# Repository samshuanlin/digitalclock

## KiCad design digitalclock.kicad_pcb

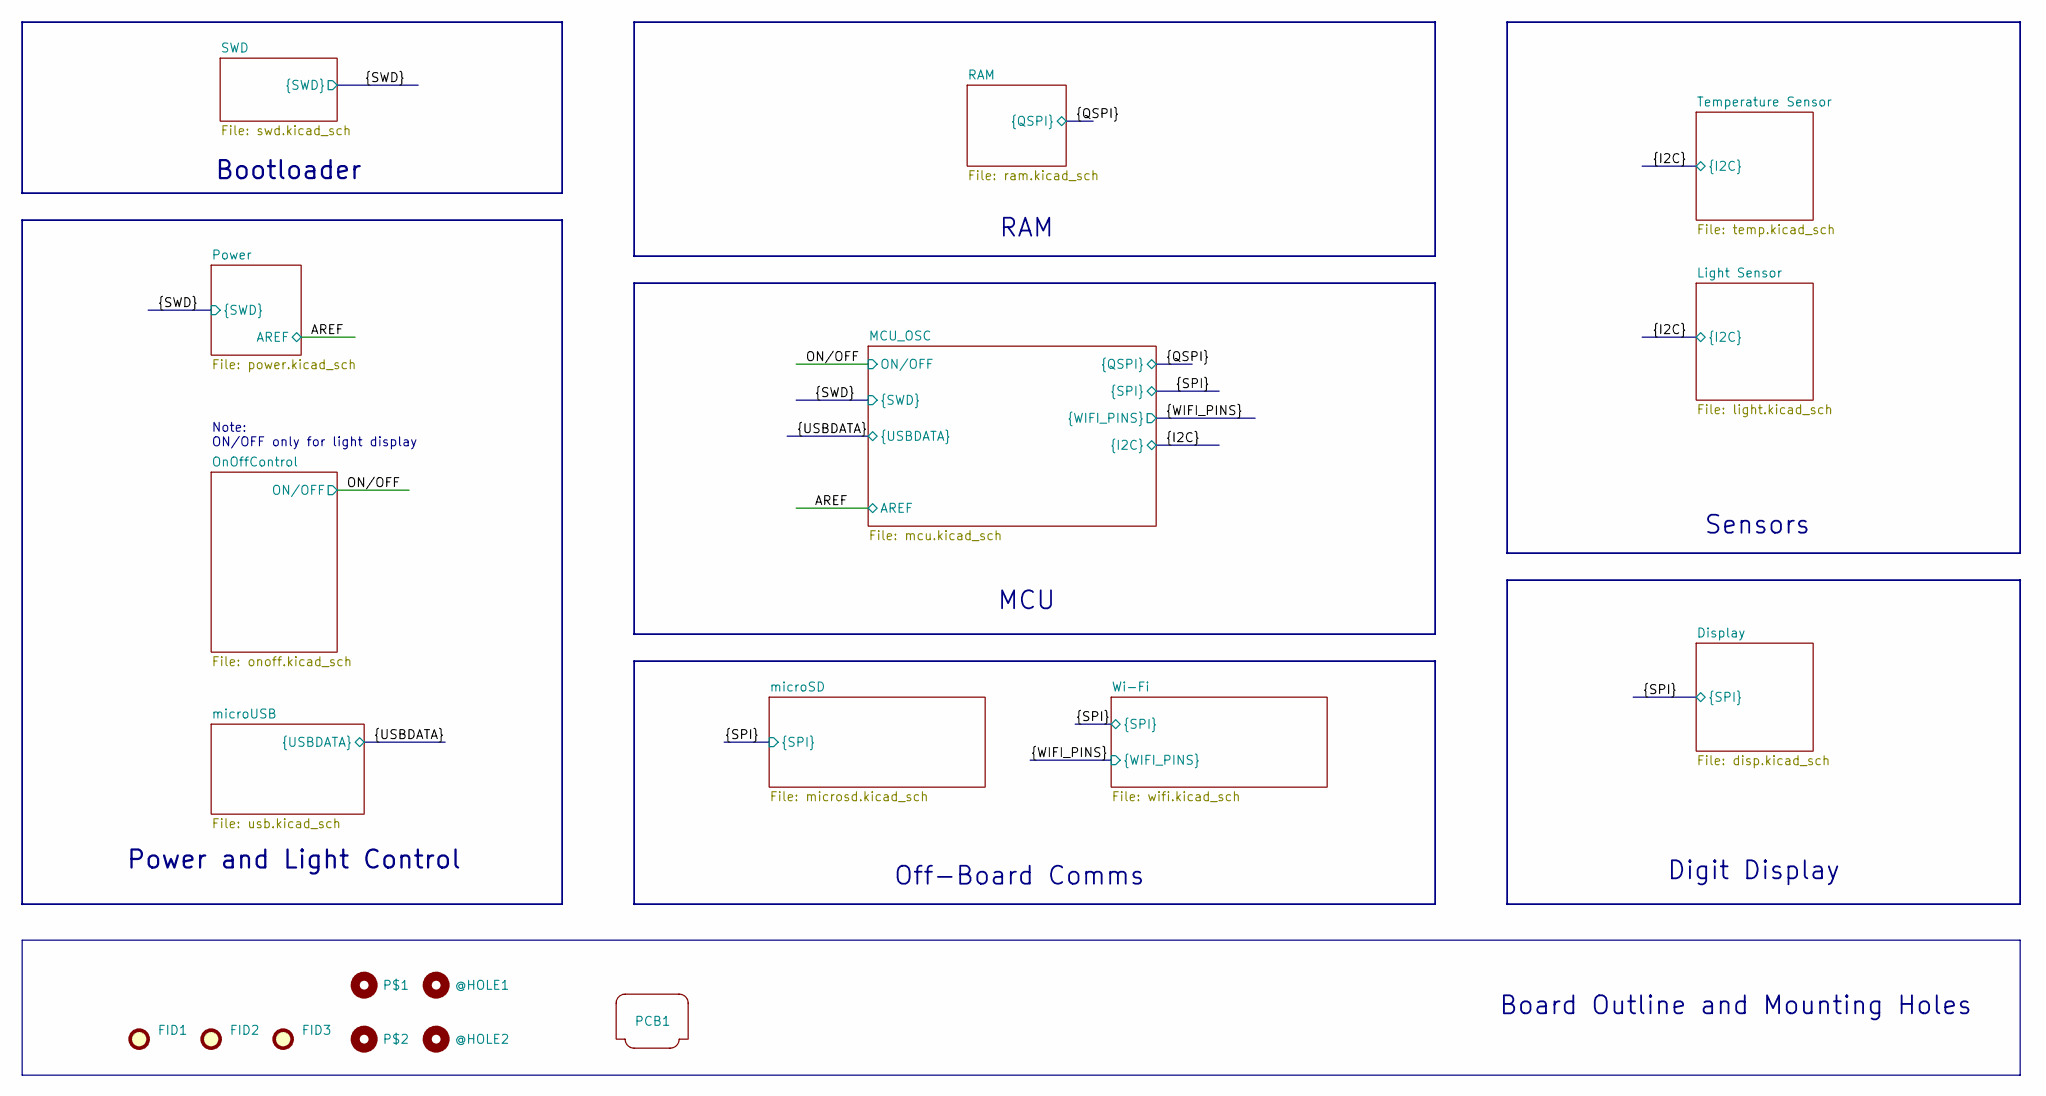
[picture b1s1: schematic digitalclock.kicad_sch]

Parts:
@HOLE1, @HOLE2: MountingHole; MountingHole_2.5mm
FID1, FID2, FID3: Fiducial; Fiducial_1mm_Mask2mm
P$1, P$2: MountingHole; MOUNTINGHOLE_2.5_PLATED
PCB1: Board_Outline

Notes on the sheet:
Sensors
Bootloader
Note: ON/OFF only for light display
RAM
MCU
Board Outline and Mounting Holes
Digit Display
Power and Light Control
Off-Board Comms

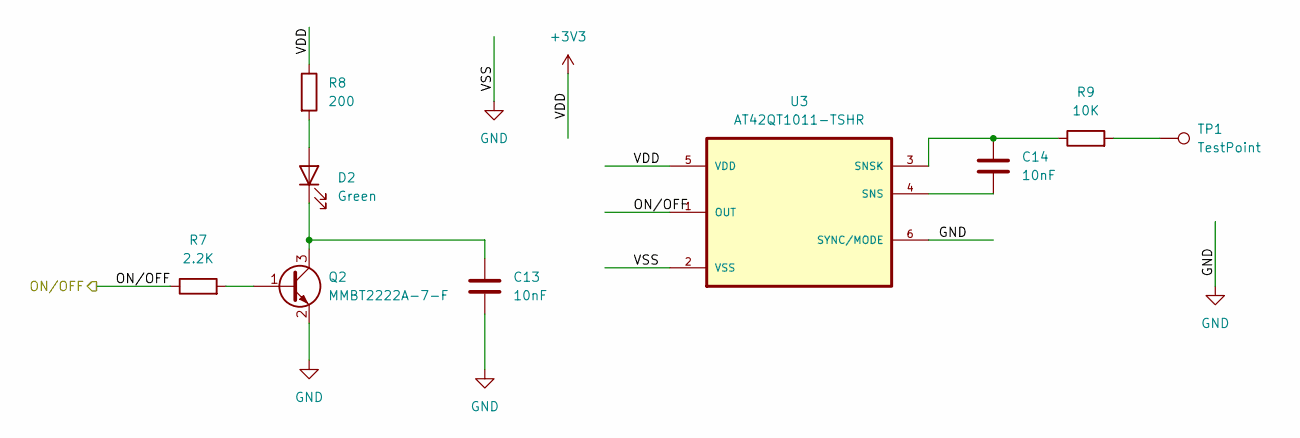
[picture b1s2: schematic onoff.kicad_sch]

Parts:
C13, C14: 10nF; 0603-NO; Mfr P/N C0402C103K3REC7411
D2: Green; 0603-NO; Mfr P/N 150060VS75000
Q2: MMBT2222A-7-F; SOT-23; Mfr P/N MMBT2222A-7-F
R7: 2.2K; 0603-NO; Mfr P/N CRGH0603F2K2
R8: 200; 0603-NO; Mfr P/N CR0603-FX-2000ELF
R9: 10K; 0603-NO; Mfr P/N RNCP0603FTD10K0
TP1: TestPoint; TestPoint_THTPad_1.0x1.0mm_Drill0.5mm
U3: AT42QT1011-TSHR; SOT95P280X145-6N; PARTREV B

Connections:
+3V3: R8.1, U3.5 (VDD); also elsewhere on the board
/ON/OFF: R7.1, U3.1 (OUT); also elsewhere on the board
GND: C13.2, Q2.2 (E), U3.2 (VSS), U3.6 (SYNC/MODE); also elsewhere on the board
unnamed: D2.2 (A), R8.2
unnamed: C13.1, D2.1 (K), Q2.3 (C)
unnamed: Q2.1 (B), R7.2
unnamed: R9.2, TP1.1
unnamed: C14.2, U3.4 (SNS)
unnamed: C14.1, R9.1, U3.3 (SNSK)

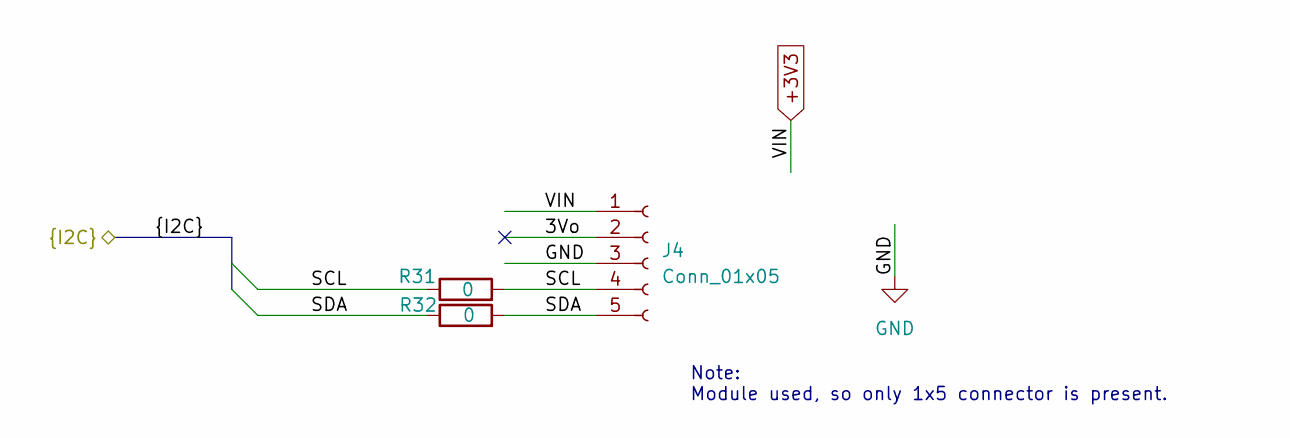
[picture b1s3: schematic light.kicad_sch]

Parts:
J4: Conn_01x05; CONN5_1LFBN-RC_SUL; Mfr P/N PPTC051LFBN-RC
R31, R32: 0; 0603-NO; Mfr P/N RC0603JR-070RL

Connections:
+3V3: J4.1; also elsewhere on the board
/Light Sensor/3Vo: J4.2
/SCL: J4.4, R31.1, R31.2; also elsewhere on the board
/SDA: J4.5, R32.1, R32.2; also elsewhere on the board
GND: J4.3; also elsewhere on the board

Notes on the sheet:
Note: Module used, so only 1x5 connector is present.

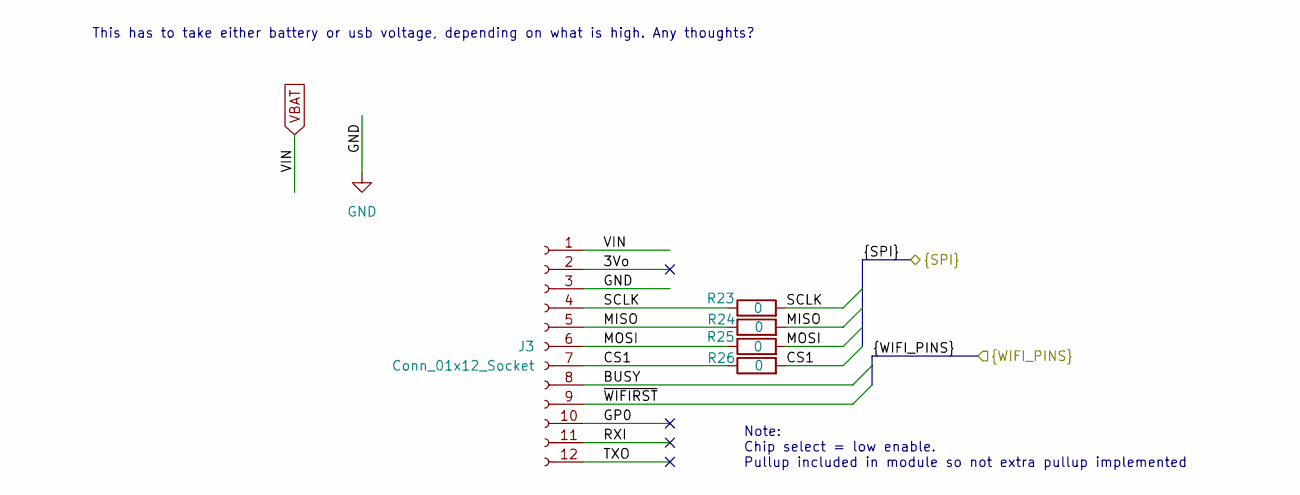
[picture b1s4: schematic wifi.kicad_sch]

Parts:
J3: Conn_01x12_Socket; PinSocket_1x12_P2.54mm_Vertical; Mfr P/N PPTC121LFBN-RC
R23, R24, R25, R26: 0; 0603-NO; Mfr P/N RC0603JR-070RL

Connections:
/BUSY: J3.8; also elsewhere on the board
/CS1: J3.7, R26.1, R26.2; also elsewhere on the board
/MISO: J3.5, R24.1, R24.2; also elsewhere on the board
/MOSI: J3.6, R25.1, R25.2; also elsewhere on the board
/SCLK: J3.4, R23.1, R23.2; also elsewhere on the board
/Wi-Fi/3Vo: J3.2
/Wi-Fi/GP0: J3.10
/Wi-Fi/RXI: J3.11
/Wi-Fi/TXO: J3.12
/~WIFIRST: J3.9; also elsewhere on the board
GND: J3.3; also elsewhere on the board
VBAT: J3.1; also elsewhere on the board

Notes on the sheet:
Note: Chip select = low enable. Pullup included in module so not extra pullup implemented
This has to take either battery or usb voltage, depending on what is high. Any thoughts?

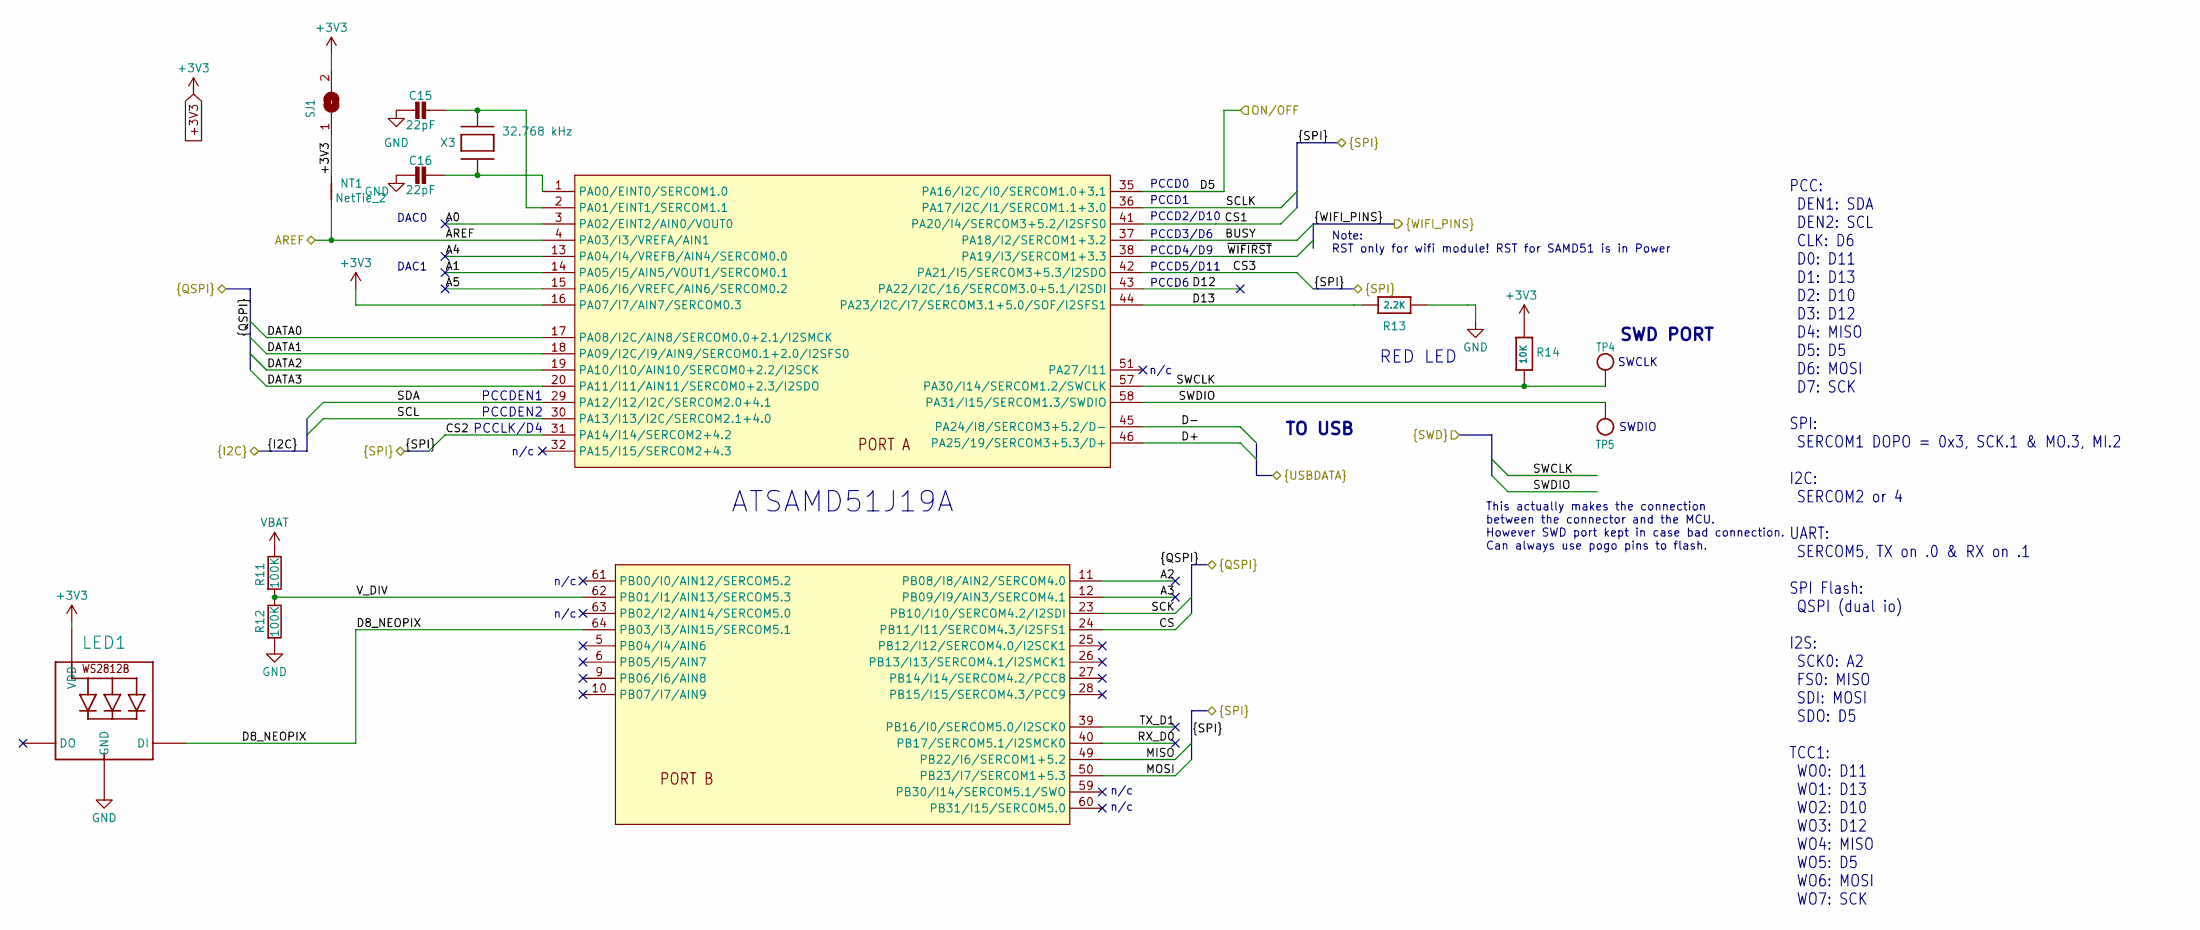
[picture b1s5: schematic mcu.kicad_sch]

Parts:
C15, C16: 22pF; 0603-NO; Mfr P/N C0603C220K4GAC7867
LED1: WS2812B3535; LED3535; Mfr P/N SK6812MINI
NT1: NetTie_2; NetTie-2_SMD_Pad0.5mm
R11, R12: 100K; 0603-NO; Mfr P/N CR0603-FX-1003ELF
R13: 2.2K; 0603-NO; Mfr P/N CRGH0603F2K2
R14: 10K; 0603-NO; Mfr P/N RNCP0603FTD10K0
SJ1: SOLDERJUMPERCLOSED; SOLDERJUMPER_CLOSEDWIRE
TP4, TP5: TESTPOINTROUND1.5MM; TESTPOINT_ROUND_1.5MM
U$1: ATSAMD51J19A-AUT; TQFP-64_10x10mm_P0.5mm; Mfr P/N ATSAMD51J19A-AUT
X3: 32.768 kHz; XTAL3215; Mfr P/N STDMUA17-32.768K

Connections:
+3V3: LED1.2 (VDD), NT1.2, R14.1, SJ1.1, SJ1.2, U$1.16 (PA07/I7/AIN7/SERCOM0.3); also elsewhere on the board
/AREF: NT1.1, U$1.4 (PA03/I3/VREFA/AIN1); also elsewhere on the board
/BUSY: U$1.37 (PA18/I2/SERCOM1+3.2); also elsewhere on the board
/CS: U$1.24 (PB11/I11/SERCOM4.3/I2SFS1); also elsewhere on the board
/CS1: U$1.41 (PA20/I4/SERCOM3+5.2/I2SFS0); also elsewhere on the board
/CS2: U$1.31 (PA14/I14/SERCOM2+4.2); also elsewhere on the board
/CS3: U$1.42 (PA21/I5/SERCOM3+5.3/I2SDO); also elsewhere on the board
/D+: U$1.46 (PA25/19/SERCOM3+5.3/D+); also elsewhere on the board
/D-: U$1.45 (PA24/I8/SERCOM3+5.2/D-); also elsewhere on the board
/DATA0: U$1.17 (PA08/I2C/AIN8/SERCOM0.0+2.1/I2SMCK); also elsewhere on the board
/DATA1: U$1.18 (PA09/I2C/I9/AIN9/SERCOM0.1+2.0/I2SFS0); also elsewhere on the board
/DATA2: U$1.19 (PA10/I10/AIN10/SERCOM0+2.2/I2SCK); also elsewhere on the board
/DATA3: U$1.20 (PA11/I11/AIN11/SERCOM0+2.3/I2SDO); also elsewhere on the board
/MCU_OSC/A0: U$1.3 (PA02/EINT2/AIN0/VOUT0)
/MCU_OSC/A1: U$1.14 (PA05/I5/AIN5/VOUT1/SERCOM0.1)
/MCU_OSC/A2: U$1.11 (PB08/I8/AIN2/SERCOM4.0)
/MCU_OSC/A3: U$1.12 (PB09/I9/AIN3/SERCOM4.1)
/MCU_OSC/A4: U$1.13 (PA04/I4/VREFB/AIN4/SERCOM0.0)
/MCU_OSC/A5: U$1.15 (PA06/I6/VREFC/AIN6/SERCOM0.2)
/MCU_OSC/D8_NEOPIX: LED1.1 (DI), U$1.64 (PB03/I3/AIN15/SERCOM5.1)
/MCU_OSC/D12: U$1.43 (PA22/I2C/16/SERCOM3.0+5.1/I2SDI)
/MCU_OSC/D13: R13.1, U$1.44 (PA23/I2C/I7/SERCOM3.1+5.0/SOF/I2SFS1)
/MCU_OSC/RX_D0: U$1.40 (PB17/SERCOM5.1/I2SMCK0)
/MCU_OSC/TX_D1: U$1.39 (PB16/I0/SERCOM5.0/I2SCK0)
/MCU_OSC/V_DIV: R11.2, R12.1, U$1.62 (PB01/I1/AIN13/SERCOM5.3)
/MISO: U$1.49 (PB22/I6/SERCOM1+5.2); also elsewhere on the board
/MOSI: U$1.50 (PB23/I7/SERCOM1+5.3); also elsewhere on the board
/ON/OFF: U$1.35 (PA16/I2C/I0/SERCOM1.0+3.1); also elsewhere on the board
/SCK: U$1.23 (PB10/I10/SERCOM4.2/I2SDI); also elsewhere on the board
/SCL: U$1.30 (PA13/I13/I2C/SERCOM2.1+4.0); also elsewhere on the board
/SCLK: U$1.36 (PA17/I2C/I1/SERCOM1.1+3.0); also elsewhere on the board
/SDA: U$1.29 (PA12/I12/I2C/SERCOM2.0+4.1); also elsewhere on the board
/SWCLK: R14.2, TP4.P$1, U$1.57 (PA30/I14/SERCOM1.2/SWCLK); also elsewhere on the board
/SWDIO: TP5.P$1, U$1.58 (PA31/I15/SERCOM1.3/SWDIO); also elsewhere on the board
/~WIFIRST: U$1.38 (PA19/I3/SERCOM1+3.3); also elsewhere on the board
GND: C15.2, C16.2, LED1.4 (GND), R12.2, R13.2; also elsewhere on the board
unnamed: C16.1, U$1.1 (PA00/EINT0/SERCOM1.0), X3.P$1
unnamed: C15.1, U$1.2 (PA01/EINT1/SERCOM1.1), X3.P$2
VBAT: R11.1; also elsewhere on the board

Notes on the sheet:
PCCD0
SWDIO
RED LED
PCCD2/D10
SWD PORT
DAC0
n/c
DAC1
PCC: DEN1: SDA DEN2: SCL CLK: D6 D0: D11 D1: D13 D2: D10 D3: D12 D4: MISO D5: D5 D6: MOSI D7: SCK SPI: SERCOM1 DOPO = 0x3, SCK.1 & MO.3, MI.2 I2C: SERCOM2 or 4 UART: SERCOM5, TX on .0 & RX on .1 SPI Flash: QSPI (dual io) I2S: SCK0: A2 FS0: MISO SDI: MOSI SDO: D5 TCC1: WO0: D11 WO1: D13 WO2: D10 WO3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
PCCD5/D11
Note: RST only for wifi module! RST for SAMD51 is in Power
PCCDEN2
TO USB
PCCLK/D4
SWCLK
PCCDEN1
PCCD6
PCCD1
ATSAMD51J19A
PCCD3/D6
This actually makes the connection between the connector and the MCU. However SWD port kept in case bad connection. Can always use pogo pins to flash.
PCCD4/D9

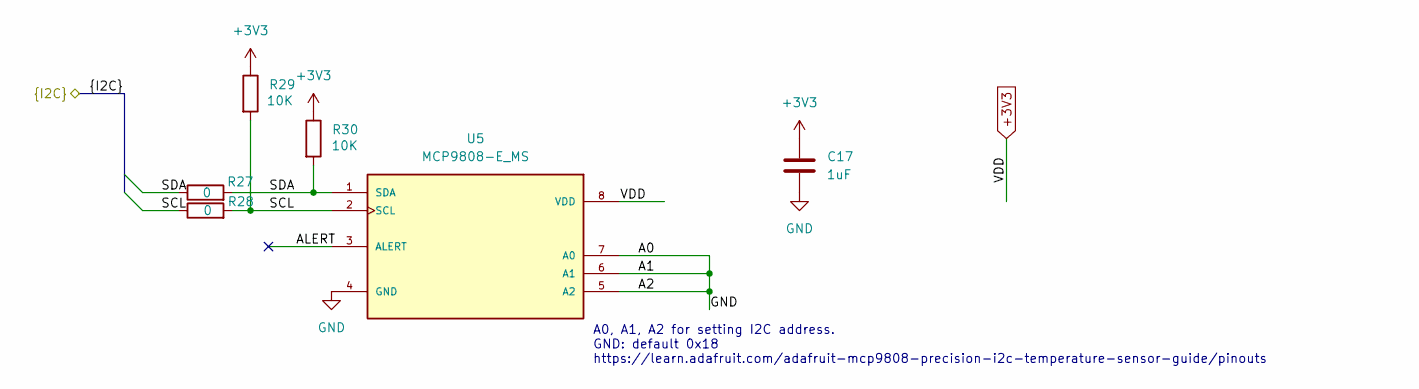
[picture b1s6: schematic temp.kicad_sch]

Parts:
C17: 1uF; C_0603_1608Metric_Pad1.08x0.95mm_HandSolder; Mfr P/N CC0603KRX7R7BB105
R27, R28: 0; 0603-NO; Mfr P/N RC0603JR-070RL
R29, R30: 10K; 0603-NO; Mfr P/N RNCP0603FTD10K0
U5: MCP9808-E_MS; SOP65P490X110-8N; Mfr P/N MCP9808-E/MS

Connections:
+3V3: C17.1, R29.1, R30.1, U5.8 (VDD); also elsewhere on the board
/SCL: R28.1, R28.2, R29.2, U5.2 (SCL); also elsewhere on the board
/SDA: R27.1, R27.2, R30.2, U5.1 (SDA); also elsewhere on the board
/Temperature Sensor/ALERT: U5.3 (ALERT)
GND: C17.2, U5.4 (GND); also elsewhere on the board

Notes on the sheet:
A0, A1, A2 for setting I2C address. GND: default 0x18 https://learn.adafruit.com/adafruit-mcp9808-precision-i2c-temperature-sensor-guide/pinouts

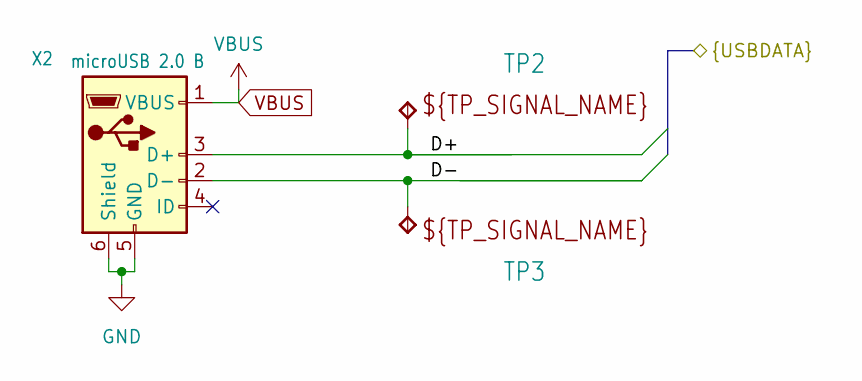
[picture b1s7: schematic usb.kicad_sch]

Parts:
TP2, TP3: B1,27_385
X2: microUSB 2.0 B; USB_Micro-B_Amphenol_10118194_Horizontal; Mfr P/N 10103594-0001LF

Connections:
/D+: TP2.TP, X2.3 (D+); also elsewhere on the board
/D-: TP3.TP, X2.2 (D-); also elsewhere on the board
GND: X2.5 (GND), X2.6 (Shield); also elsewhere on the board
VBUS: X2.1 (VBUS); also elsewhere on the board

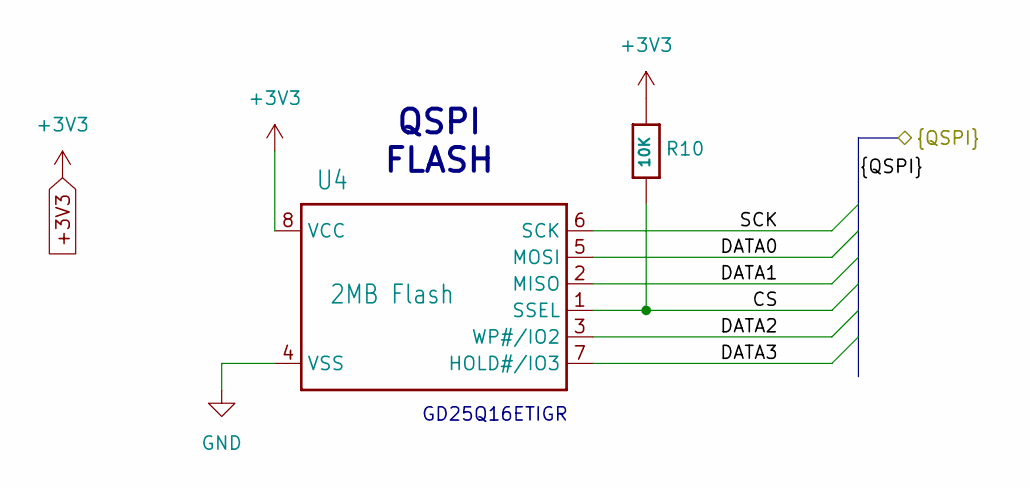
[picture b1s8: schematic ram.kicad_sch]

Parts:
R10: 10K; 0603-NO; Mfr P/N RNCP0603FTD10K0
U4: 2MB Flash; SOIC-8_3.9x4.9mm_P1.27mm; Mfr P/N GD25Q16ETIGR

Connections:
+3V3: R10.1, U4.8 (VCC); also elsewhere on the board
/CS: R10.2, U4.1 (SSEL); also elsewhere on the board
/DATA0: U4.5 (MOSI); also elsewhere on the board
/DATA1: U4.2 (MISO); also elsewhere on the board
/DATA2: U4.3 (WP#/IO2); also elsewhere on the board
/DATA3: U4.7 (HOLD#/IO3); also elsewhere on the board
/SCK: U4.6 (SCK); also elsewhere on the board
GND: U4.4 (VSS); also elsewhere on the board

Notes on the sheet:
QSPI FLASH
GD25Q16ETIGR

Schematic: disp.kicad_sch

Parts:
J5, J6, J7, J8: Conn_01x07_Socket; PinHeader_1x07_P2.54mm_Vertical; Mfr P/N PH1-07-UA
R33, R34, R35, R38, R39, R40: 0; 0603-NO; Mfr P/N RC0603JR-070RL
R36: 10K; 0603-NO; Mfr P/N RNCP0603FTD10K0
R37, R41: 9.53k; 0603-NO; Mfr P/N CR0603-FX-9531ELF
U6: MAX7221CWGT+; SOIC127P1032X265-24N; Mfr P/N MAX7221CWG+T
U7: MAX7221CWGT; SOIC127P1032X265-24N; Mfr P/N MAX7221CWG+T

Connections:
/CS3: R35.1, R35.2, R36.2, R40.1, R40.2, U6.12 (~CS), U7.12 (~CS); also elsewhere on the board
/Display/A: J6.2, J8.2, U6.14 (SEG_A), U7.14 (SEG_A)
/Display/B: J6.3, J8.3, U6.16 (SEG_B), U7.16 (SEG_B)
/Display/BLUE_1: J6.5, U6.2 (DIG_0)
/Display/BLUE_2: J6.7, U6.3 (DIG_4)
/Display/BLUE_3: J8.5, U7.2 (DIG_0)
/Display/BLUE_4: J8.7, U7.3 (DIG_4)
/Display/C: J6.6, J8.6, U6.20 (SEG_C), U7.20 (SEG_C)
/Display/D: J5.2, J7.2, U6.23 (SEG_D), U7.23 (SEG_D)
/Display/DP: J5.3, J7.3, U6.22 (SEG_DP), U7.22 (SEG_DP)
/Display/E: J5.1, J7.1, U6.21 (SEG_E), U7.21 (SEG_E)
/Display/F: J5.5, J7.5, U6.15 (SEG_F), U7.15 (SEG_F)
/Display/G: J5.6, J7.6, U6.17 (SEG_G), U7.17 (SEG_G)
/Display/GREEN_1: J6.4, U6.11 (DIG_1)
/Display/GREEN_2: J5.7, U6.10 (DIG_5)
/Display/GREEN_3: J8.4, U7.11 (DIG_1)
/Display/GREEN_4: J7.7, U7.10 (DIG_5)
/Display/RED_1: J6.1, U6.6 (DIG_2)
/Display/RED_2: J5.4, U6.5 (DIG_6)
/Display/RED_3: J8.1, U7.6 (DIG_2)
/Display/RED_4: J7.4, U7.5 (DIG_6)
/MOSI: R34.1, R34.2, R39.1, R39.2, U6.1 (DIN), U7.1 (DIN); also elsewhere on the board
/SCLK: R33.1, R33.2, R38.1, R38.2, U6.13 (CLK), U7.13 (CLK); also elsewhere on the board
GND: U6.4 (GND), U6.9 (GND__1), U7.4 (GND), U7.9 (GND__1); also elsewhere on the board
unnamed: R37.2, U6.18 (ISET)
unnamed: R41.2, U7.18 (ISET)
VBAT: R36.1, R37.1, R41.1, U6.19 (V+), U7.19 (V+); also elsewhere on the board

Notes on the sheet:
D3 D4
Note: Reviewed the Power sheet. VBAT should still be enabled when BAT not plugged in As long as VBUS connected
Pin 1
Pin 14
Note: low enabled ~{CS} needs pullup both chips share the same ~{CS} so only one pullup
D1 D2

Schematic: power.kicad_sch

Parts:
C1, C4, C5, C6, C9: 10µF; 0805-NO; Mfr P/N CL21A106KOQNNNE
C2, C3, C7, C8, C10, C11, C12: 1uF; C_0603_1608Metric_Pad1.08x0.95mm_HandSolder; Mfr P/N CC0603KRX7R7BB105
CHG1: ORANGE; CHIPLED_0805_NOOUTLINE; Mfr P/N B1701UD--20D000414U1930
D1: MBR120; SOD-123; Mfr P/N MBR120LSFT1G
L1: 10uH; INDUCTOR_1007; Mfr P/N LSQEA251818T100K
Q1: DMP2070UQ-7; SOT23-R; Mfr P/N DMP2070UQ-7
R1: 1K; 0603-NO; Mfr P/N MCT06030C1001FP500
R2, R4, R5: 10K; 0603-NO; Mfr P/N RNCP0603FTD10K0
R3: 100K; 0603-NO; Mfr P/N CR0603-FX-1003ELF
R6: 100K; R_Array_Convex_4x0603; Mfr P/N CAY16-1003F4LF; not fitted
SW1: KMR2; BTN_KMR2_4.6X2.8; Mfr P/N KMR241NG ULC LFS
U1: MCP73831T-2ACI/OT; SOT23-5; Mfr P/N MCP73831T-2ATI/OT
U2: AP2112-3.3; SOT-23-5; Mfr P/N AP2112K-3.3TRG1
U$1: ATSAMD51J19A-AUT; TQFP-64_10x10mm_P0.5mm; Mfr P/N ATSAMD51J19A-AUT
X1: JSTPH; JST_PH_S2B-PH-SM4-TB_1x02-1MP_P2.00mm_Horizontal; Mfr P/N S2B-PH-SM4-TB

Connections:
+3V3: C6.1, C7.1, C9.1, C10.1, C11.1, C12.1, R4.1, U2.5 (VOUT), U$1.8 (VDDANA), U$1.21 (VDDIO_0), U$1.34 (VDDIO_1), U$1.48 (VDDIO_2), U$1.56 (VDDIO_3); also elsewhere on the board
/AREF: C8.1; also elsewhere on the board
/Power/EN: R5.2, U2.3 (EN)
/Power/Vin: C4.1, D1.C, Q1.2 (S), R5.1, U2.1 (VIN)
/~RST: C2.1, R4.2, SW1.A, SW1.A' (P1), U$1.52 (~RESET); also elsewhere on the board
GND: C1.2, C2.2, C3.2, C4.2, C5.2, C6.2, C7.2, C8.2, C9.2, C10.2, C11.2, C12.2, R2.2, R3.2, SW1.B (S), SW1.B' (S1), U1.2 (VSS), U2.2 (GND), U$1.7 (GND_0), U$1.22 (GND_1), U$1.33 (GND_2), U$1.47 (GND_3), U$1.54 (GND_4), X1.1; also elsewhere on the board
unnamed: CHG1.C, R1.1
unnamed: C3.1, C5.1, L1.P$1 (1), U$1.53 (VDDCORE)
unnamed: L1.P$2 (2), U$1.55 (VSW)
unnamed: R2.1, U1.5 (PROG)
unnamed: R1.2, U1.1 (STAT)
VBAT: C1.1, Q1.3 (D), U1.3 (VBAT), X1.2; also elsewhere on the board
VBUS: CHG1.A, D1.A, Q1.1 (G), R3.1, U1.4 (VDD); also elsewhere on the board

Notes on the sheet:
RESET
10K = 100mA
1.0K = 1000mA
2.0K = 500mA
not used
ATSAMD51J19A
POWER AND FILTERING
Bypass capacitors?
USB AND BATTERY CHARGING
Try connecting to VBAT and see if VBUS is able to supply power to VBAT
5.0K = 200mA

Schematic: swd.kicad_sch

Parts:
J1: AMPHENOL_20021521-00010T4LF; Mfr P/N 20021521-00010T4LF

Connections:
+3V3: J1.1; also elsewhere on the board
/SWCLK: J1.4; also elsewhere on the board
/SWD/Key: J1.7
/SWD/SWO: J1.6
/SWD/n/c: J1.8
/SWDIO: J1.2; also elsewhere on the board
/~RST: J1.10; also elsewhere on the board
GND: J1.3, J1.5, J1.9; also elsewhere on the board

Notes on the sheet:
Note: Routed based on pinouts listed here: https://developer.arm.com/documentation/101636/0100/Debug-and-Trace/JTAG-SWD-Interface

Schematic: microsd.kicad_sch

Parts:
J2: MEM2075-00-140-01-A; GCT_MEM2075-00-140-01-A; PARTREV A
R15, R16, R17, R18: 0; 0603-NO; Mfr P/N RC0603JR-070RL
R19, R20, R21, R22: 47K; 0603-NO; Mfr P/N CR0603-FX-4702ELF

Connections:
+3V3: J2.P4 (VDD), R19.1, R20.1, R21.1, R22.1; also elsewhere on the board
/CS2: J2.P2 (~CS), R18.1, R18.2, R22.2; also elsewhere on the board
/MISO: J2.P7 (MISO), R16.1, R16.2, R20.2; also elsewhere on the board
/MOSI: J2.P3 (MOSI), R17.1, R17.2, R21.2; also elsewhere on the board
/SCLK: J2.P5 (CLK), R15.1, R15.2, R19.2; also elsewhere on the board
GND: J2.P6 (VSS), J2.SH1 (SHIELD), J2.SH2 (SHIELD__1), J2.SH3 (SHIELD__2), J2.SH4 (SHIELD__3); also elsewhere on the board

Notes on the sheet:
add in resistors for sd card
Note: Neg enabled ~{CS} needs pullup

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
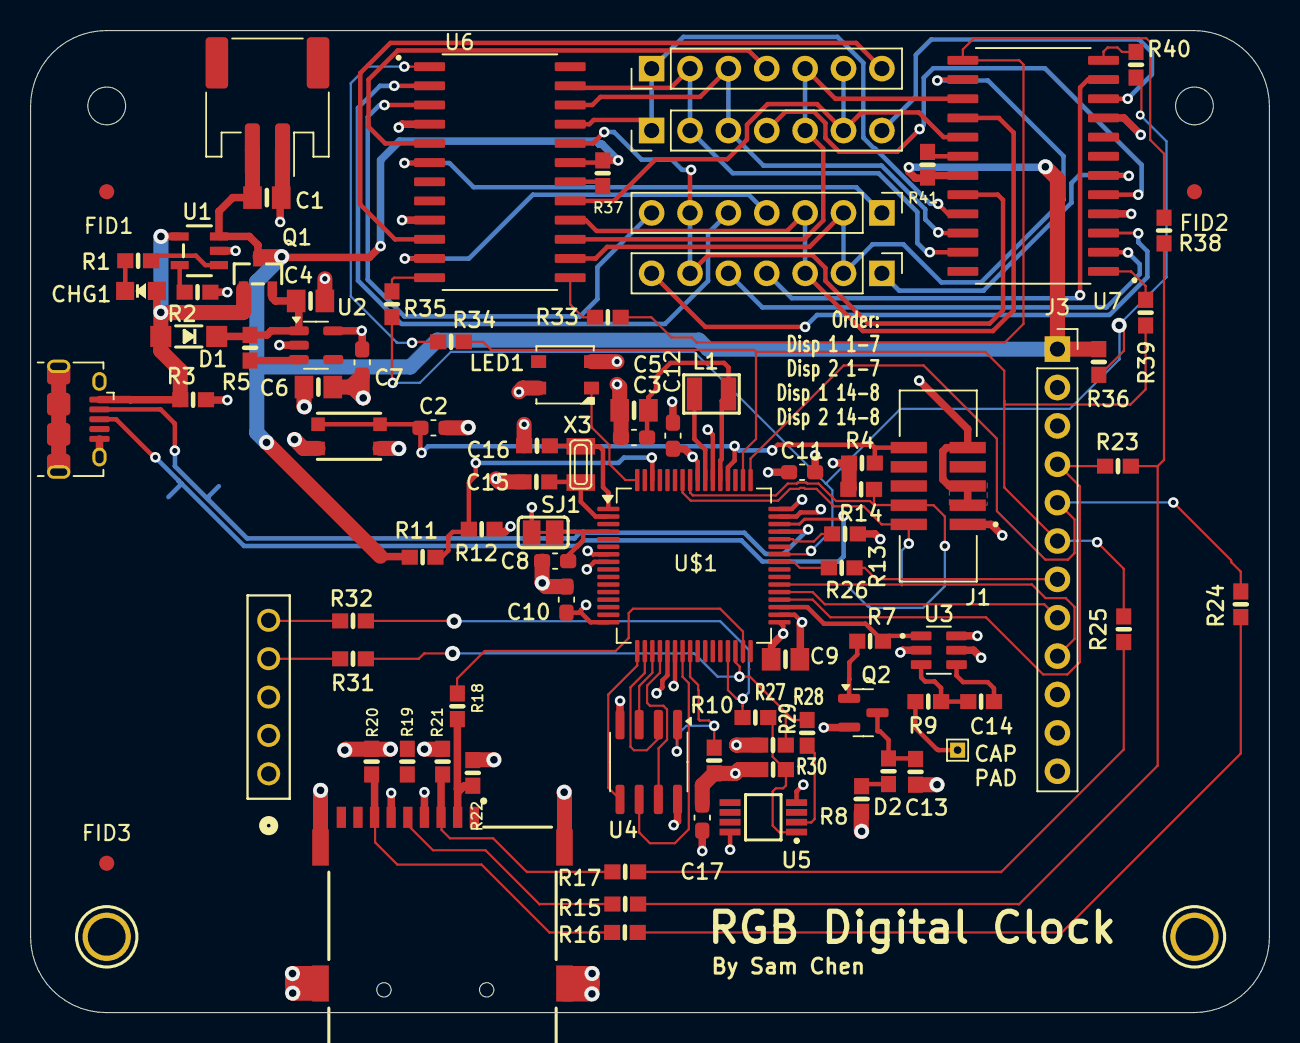
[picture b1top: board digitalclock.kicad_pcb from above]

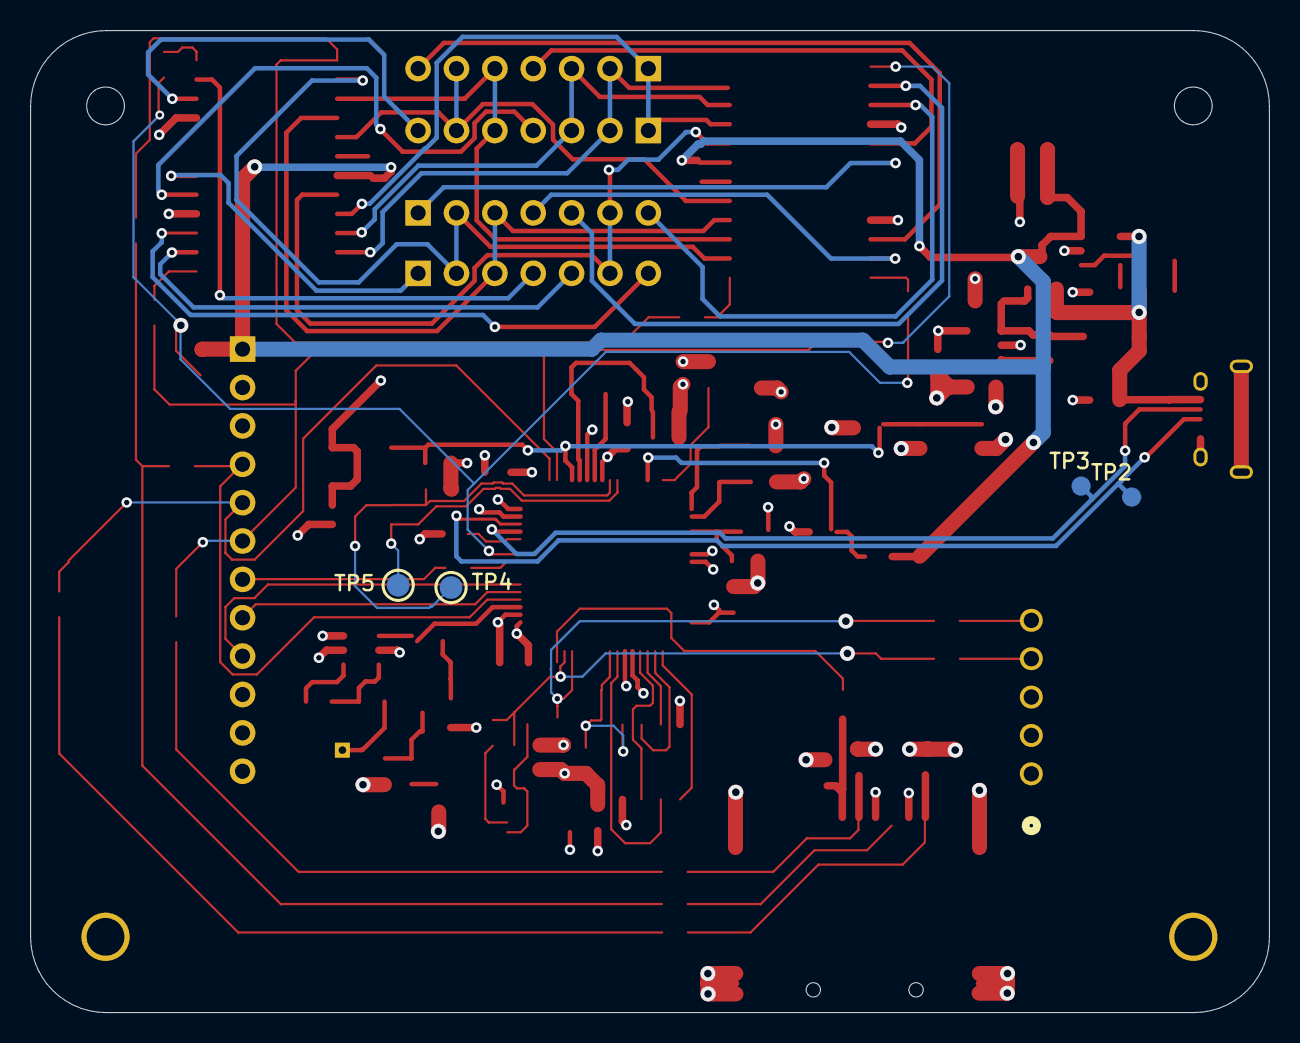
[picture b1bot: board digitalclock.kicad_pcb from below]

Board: 4 copper layers, 82.0 x 65.0 mm, 99 parts (4 on the bottom side), 67 nets.

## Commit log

2024-11-04 Added 0ohm resistors and TPs
2024-11-05 Updated BOM, created fab outputs
2024-12-09 Final project submission
